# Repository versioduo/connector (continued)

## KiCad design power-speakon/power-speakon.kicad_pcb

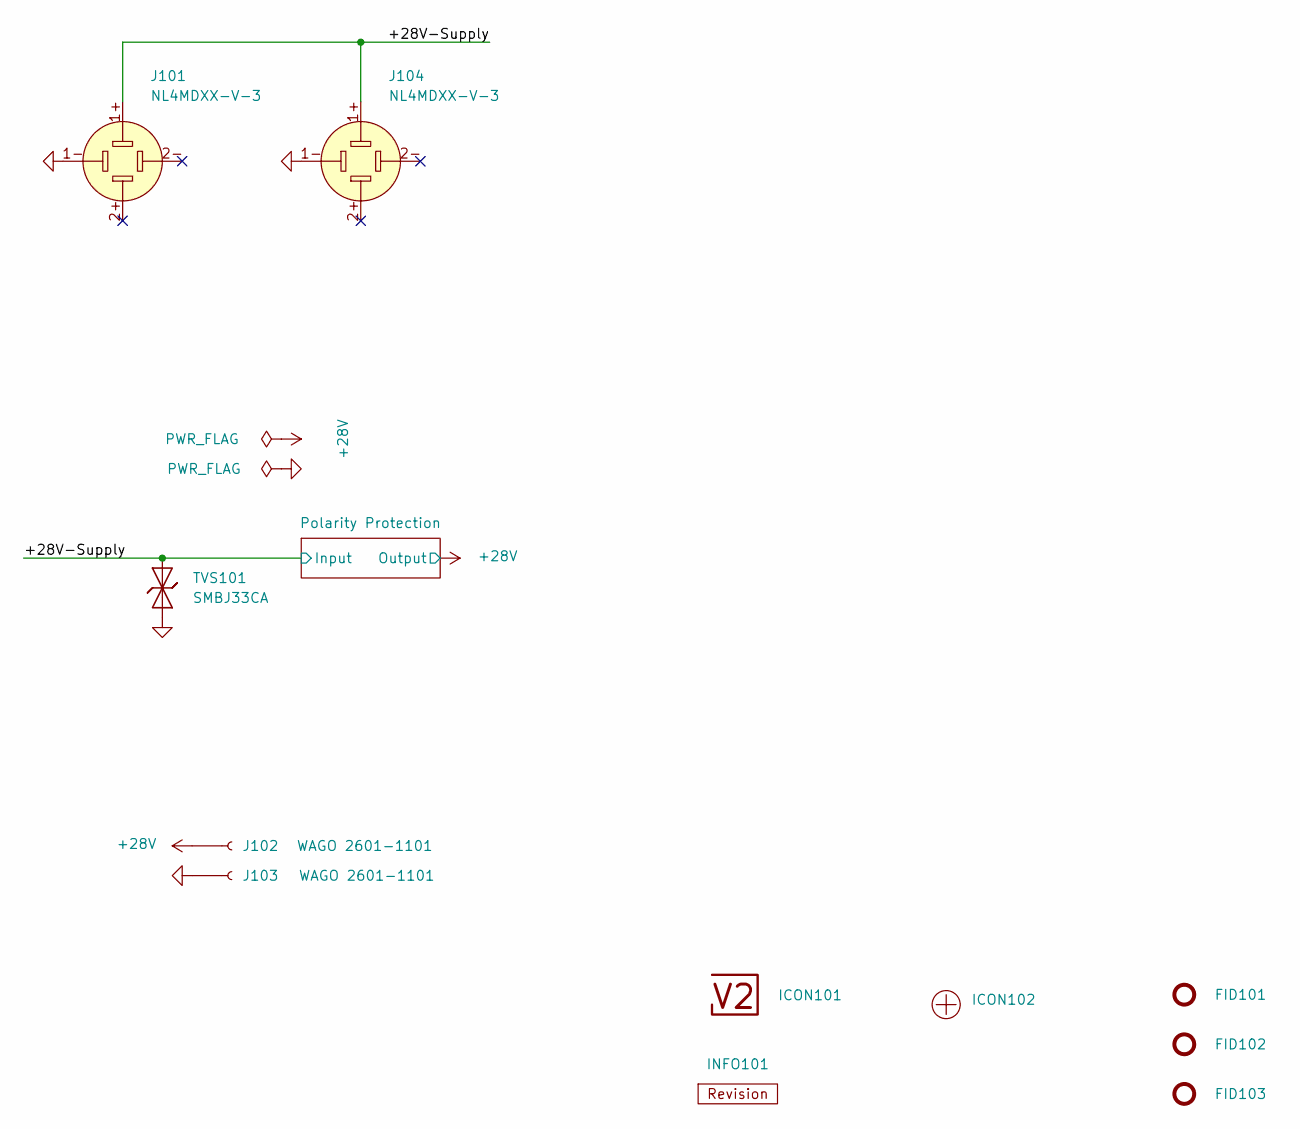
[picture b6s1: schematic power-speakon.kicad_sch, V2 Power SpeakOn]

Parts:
FID101, FID102, FID103: Fiducial_Paste; Fiducial_0.5mm_Mask1mm_Paste
ICON101: V2-logo; Logo_Small
ICON102: Plus; Plus_Small
INFO101: Revision
J101, J104: NL4MDXX-V-3; Mouser 568-NL4MDXXV3
J102, J103: WAGO 2601-1101; 2601-1101; Rating 17.5A
TVS101: SMBJ33CA; D_SMB; Rating 33V; Mouser 652-SMBJ33CA-Q

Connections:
+28V: J102.1; also elsewhere on the board
/+28V-Supply: J101.1+, J104.1+, TVS101.2 (A); also elsewhere on the board
GND: J101.1-, J103.1, J104.1-, TVS101.1 (K); also elsewhere on the board

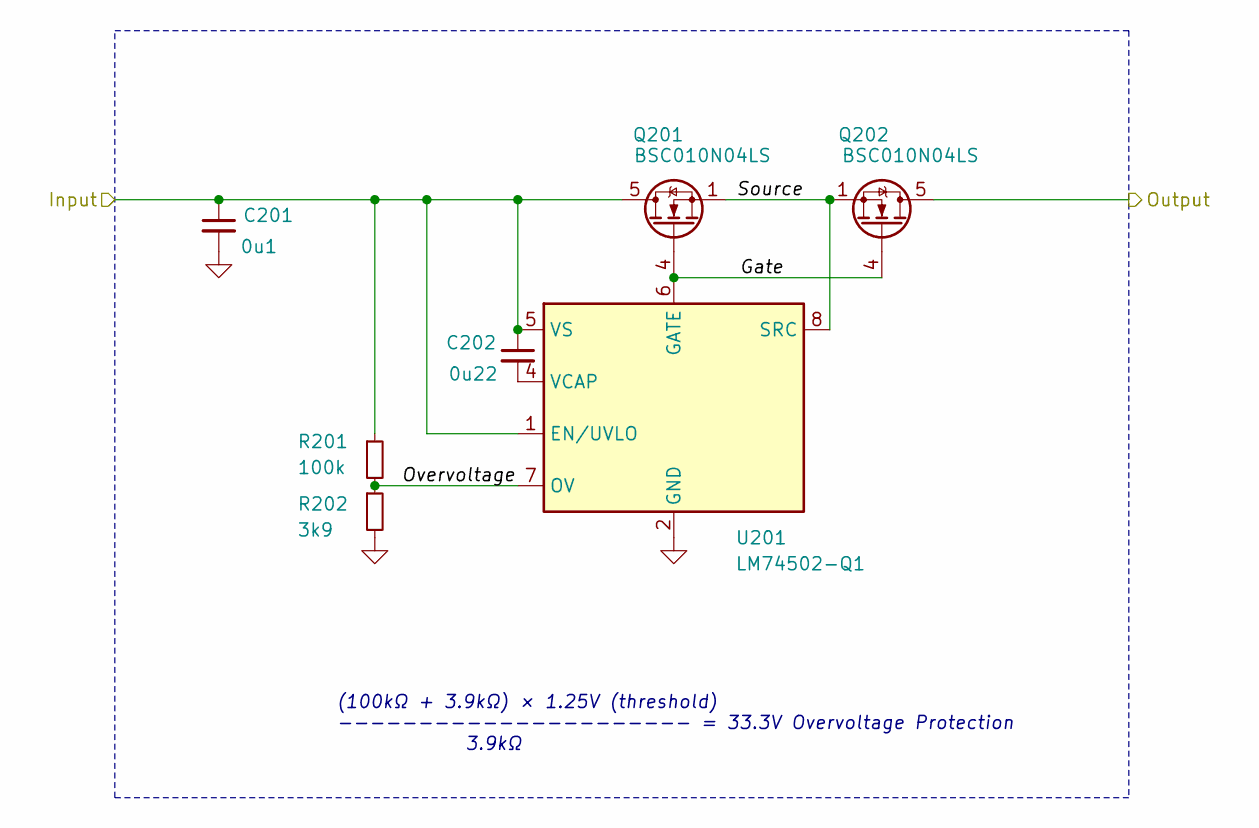
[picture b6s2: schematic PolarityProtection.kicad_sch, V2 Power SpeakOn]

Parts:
C201: 0u1; C_1608; Rating 50V; Mouser 810-CGA3E2X7R1H104MA
C202: 0u22; C_1608; Rating 50V; Mouser 603-CC0603JRX79BB224
Q201, Q202: BSC010N04LS; TDSON-8-FL; Rating 40V; Mouser 726-BSC010N04LS
R201: 100k; R_1608; Rating 100mW; Mouser 71-CRCW0603100KFKEAC
R202: 3k9; R_1608; Rating 100mW; Mouser 71-CRCW06033K90FKEAC
U201: LM74502-Q1; SOT-23-8; Rating 60uA; Mouser 595-LM74502QDDFRQ1

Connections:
+28V: Q202.5 (D); also elsewhere on the board
/+28V-Supply: C201.1, C202.1, Q201.5 (D), R201.1, U201.1 (EN/UVLO), U201.5 (VS); also elsewhere on the board
/Polarity Protection/Gate: Q201.4 (G), Q202.4 (G), U201.6 (GATE)
/Polarity Protection/Overvoltage: R201.2, R202.1, U201.7 (OV)
/Polarity Protection/Source: Q201.1 (S), Q202.1 (S), U201.8 (SRC)
GND: C201.2, R202.2, U201.2 (GND); also elsewhere on the board
unnamed: C202.2, U201.4 (VCAP)

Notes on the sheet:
(100kΩ + 3.9kΩ) × 1.25V (threshold) ---------------------- = 33.3V Overvoltage Protection 3.9kΩ

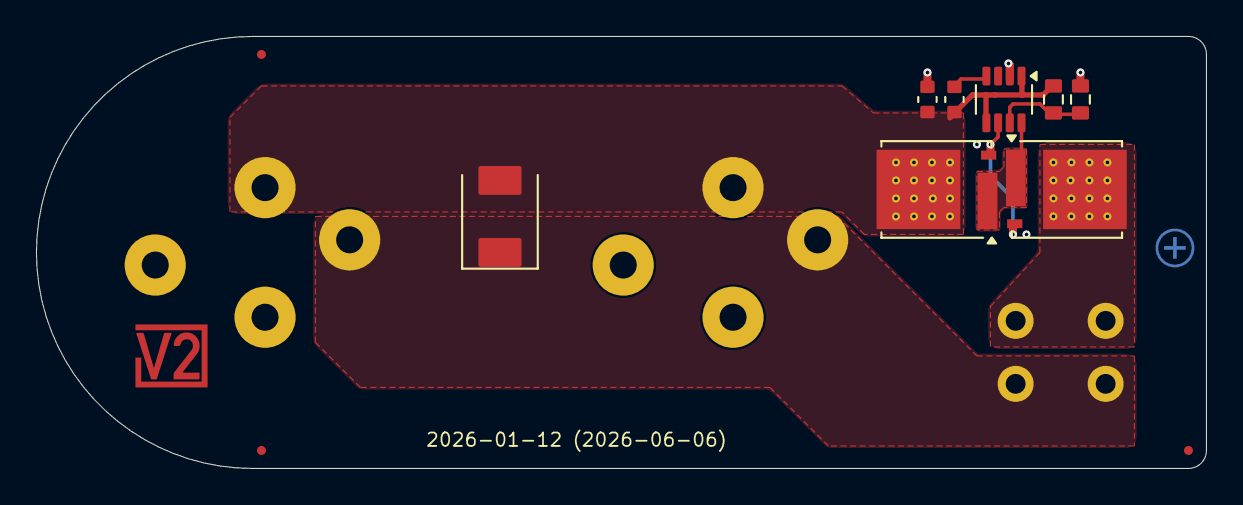
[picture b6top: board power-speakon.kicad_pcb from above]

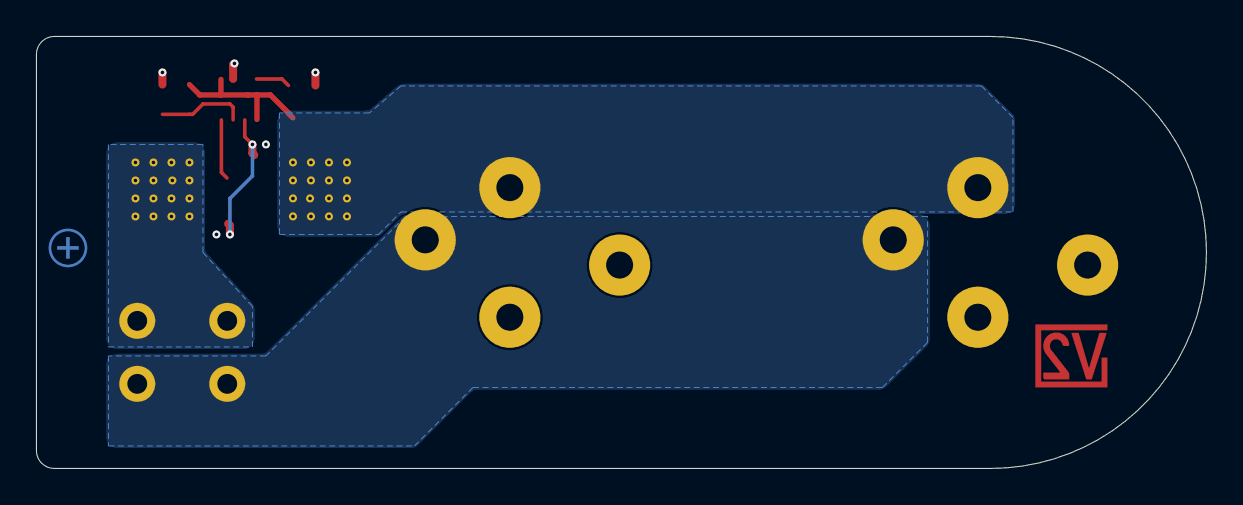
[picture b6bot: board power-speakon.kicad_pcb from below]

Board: 4 copper layers, 65.0 x 24.0 mm, 18 parts (5 on the bottom side), 7 nets.

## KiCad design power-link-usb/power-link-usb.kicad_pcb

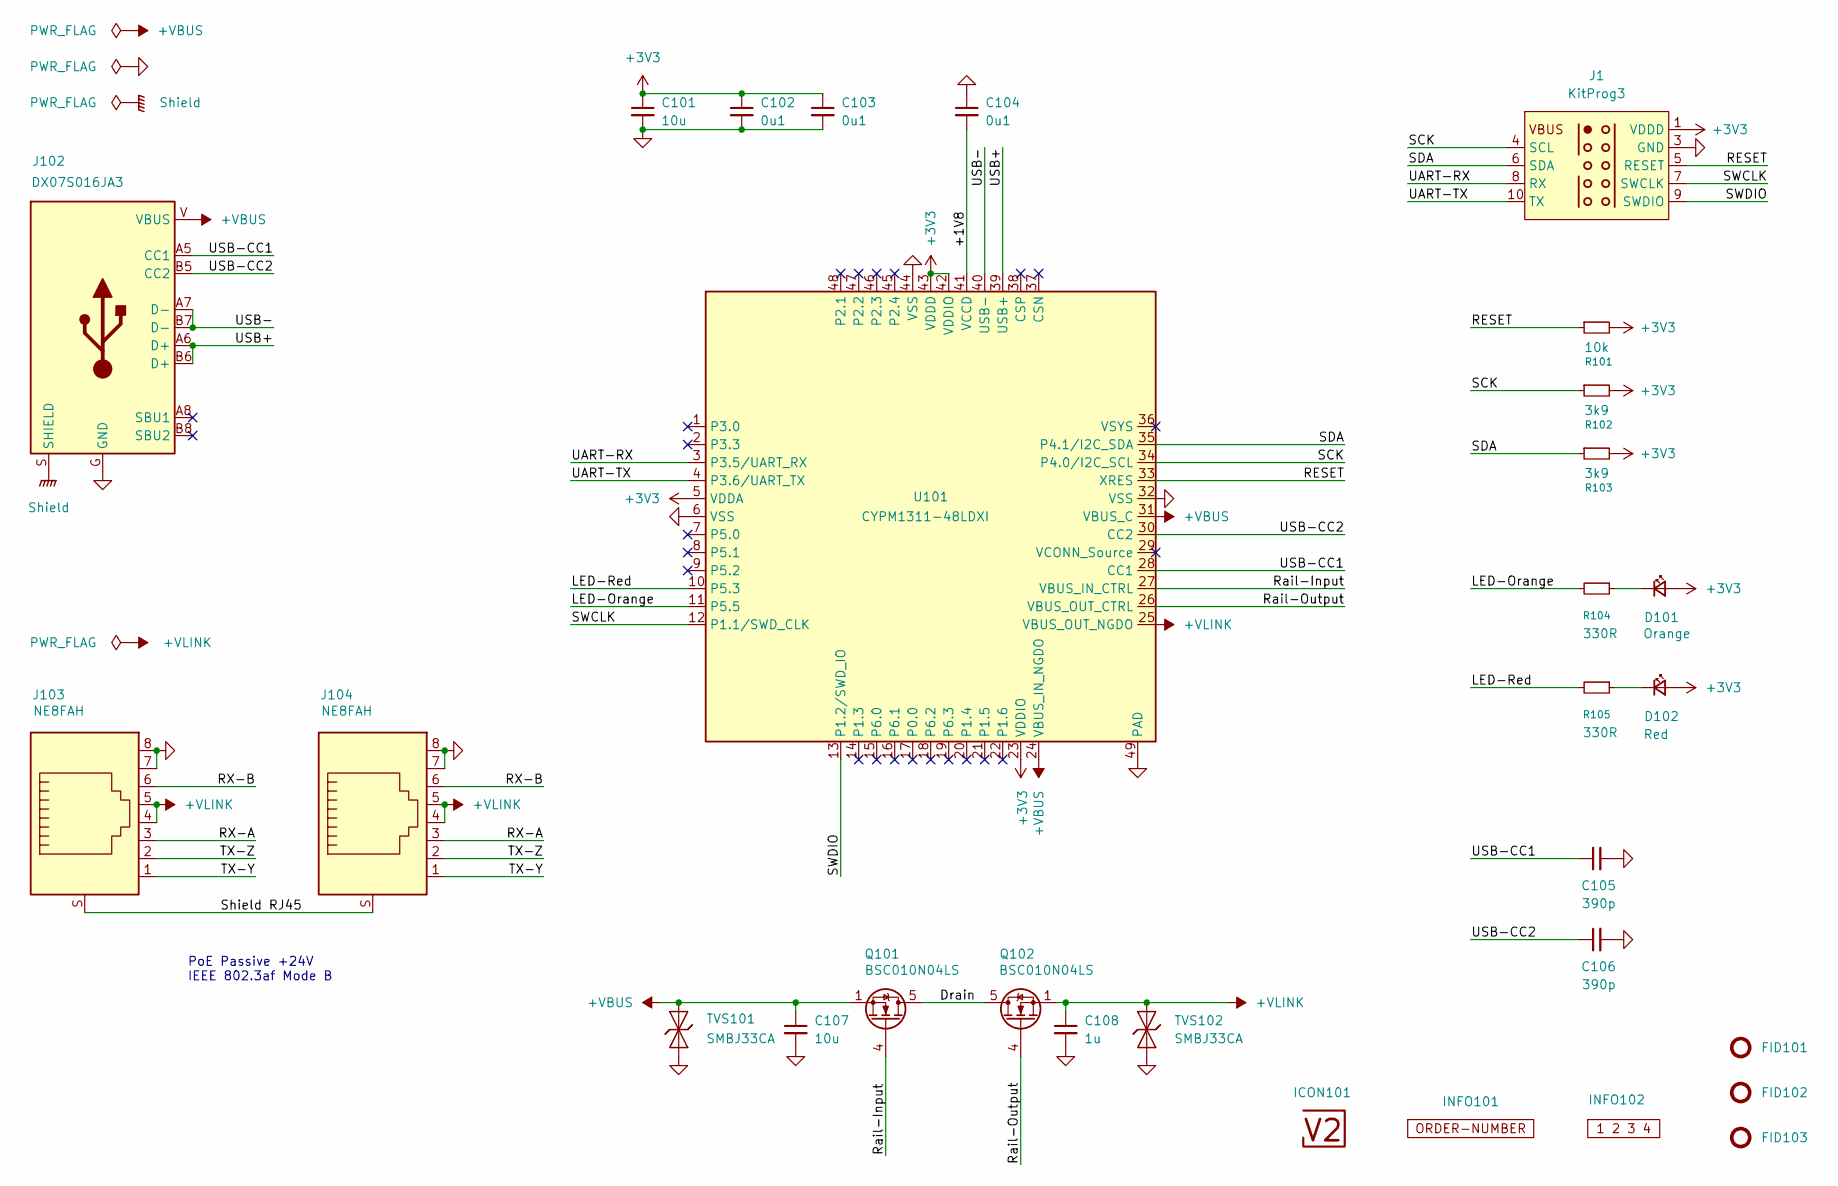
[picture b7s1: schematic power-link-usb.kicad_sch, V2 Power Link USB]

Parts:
C101: 10u; C_0603; Rating 10V; Mouser 810-C1608X6S1A106M
C102, C103, C104: 0u1; C_0603; Rating 50V; Mouser 810-CGA3E2X7R1H104MA
C105, C106: 390p; C_0603; Rating 50V; Mouser 810-CGA3E2C0G1H391J
C107: 10u; C_0805; Rating 25V; Mouser 810-C2012X5R1E106K
C108: 1u; C_0603; Rating 50V; Mouser 810-CGA3E3X7R1H105K0
D101: Orange; LED_0603; Mouser 755-SML-D12D1WT86
D102: Red; LED_0603; Mouser 755-SML-D12V1WT86
FID101, FID102, FID103: Fiducial_Paste; Fiducial_0.5mm_Mask1mm_Paste
ICON101: V2-logo; Logo_Small
INFO101: Order_Number
INFO102: Layer_Numbers
J1: KitProg3
J102: DX07S016JA3; JAE_DX07S016JA3; Mouser 656-DX07S016JA3R1500
J103, J104: NE8FAH; Mouser 568-NE8FAH
Q101, Q102: BSC010N04LS; TDSON-8-FL; Rating 40V; Mouser 726-BSC010N04LS
R101: 10k; R_0603; Rating 100mW; Mouser 71-CRCW060310K0FKEAC
R102, R103: 3k9; R_0603; Rating 100mW; Mouser 71-CRCW06033K90FKEAC
R104, R105: 330R; R_0603; Rating 100mW; Mouser 71-CRCW0603330RFKEAC
TVS101, TVS102: SMBJ33CA; D_SMB; Rating 33V; Mouser 652-SMBJ33CA-Q
U101: CYPM1311-48LDXI; QFN-48-1EP_6x6mm_P0.4mm_EP4.6x4.6mm; Mouser 727-CYPM1311-48LDXI

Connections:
+3V3: C101.1, C102.1, C103.1, D101.2 (A), D102.2 (A), J1.1 (VDDD), R101.2, R102.2, R103.2, U101.5 (VDDA), U101.23 (VDDIO), U101.42 (VDDIO), U101.43 (VDDD)
+VBUS: C107.1, J102.V (VBUS), Q101.1 (S), TVS101.2 (A), U101.24 (VBUS_IN_NGDO), U101.31 (VBUS_C)
+VLINK: C108.1, J103.4, J103.5, J104.4, J104.5, Q102.1 (S), TVS102.2 (A), U101.25 (VBUS_OUT_NGDO)
/+1V8: C104.2, U101.41 (VCCD)
/Drain: Q101.5 (D), Q102.5 (D)
/LED-Orange: R104.2, U101.11 (P5.5)
/LED-Red: R105.2, U101.10 (P5.3)
/RESET: J1.5 (RESET), R101.1, U101.33 (XRES)
/RX-A: J103.3, J104.3
/RX-B: J103.6, J104.6
/Rail-Input: Q101.4 (G), U101.27 (VBUS_IN_CTRL)
/Rail-Output: Q102.4 (G), U101.26 (VBUS_OUT_CTRL)
/SCK: J1.4 (SCL), R102.1, U101.34 (P4.0/I2C_SCL)
/SDA: J1.6 (SDA), R103.1, U101.35 (P4.1/I2C_SDA)
/SWCLK: J1.7 (SWCLK), U101.12 (P1.1/SWD_CLK)
/SWDIO: J1.9 (SWDIO), U101.13 (P1.2/SWD_IO)
/Shield RJ45: J103.S, J104.S
/TX-Y: J103.1, J104.1
/TX-Z: J103.2, J104.2
/UART-RX: J1.8 (RX), U101.3 (P3.5/UART_RX)
/UART-TX: J1.10 (TX), U101.4 (P3.6/UART_TX)
/USB+: J102.A6 (D+), J102.B6 (D+), U101.39 (USB+)
/USB-: J102.A7 (D-), J102.B7 (D-), U101.40 (USB-)
/USB-CC1: C105.1, J102.A5 (CC1), U101.28 (CC1)
/USB-CC2: C106.1, J102.B5 (CC2), U101.30 (CC2)
GND: C101.2, C102.2, C103.2, C104.1, C105.2, C106.2, C107.2, C108.2, J1.3 (GND), J102.G (GND), J103.7, J103.8, J104.7, J104.8, TVS101.1 (K), TVS102.1 (K), U101.6 (VSS), U101.32 (VSS), U101.44 (VSS), U101.49 (PAD)
unnamed: D101.1 (K), R104.1
unnamed: D102.1 (K), R105.1
Shield: J102.S (SHIELD)

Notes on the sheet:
PoE Passive +24V IEEE 802.3af Mode B

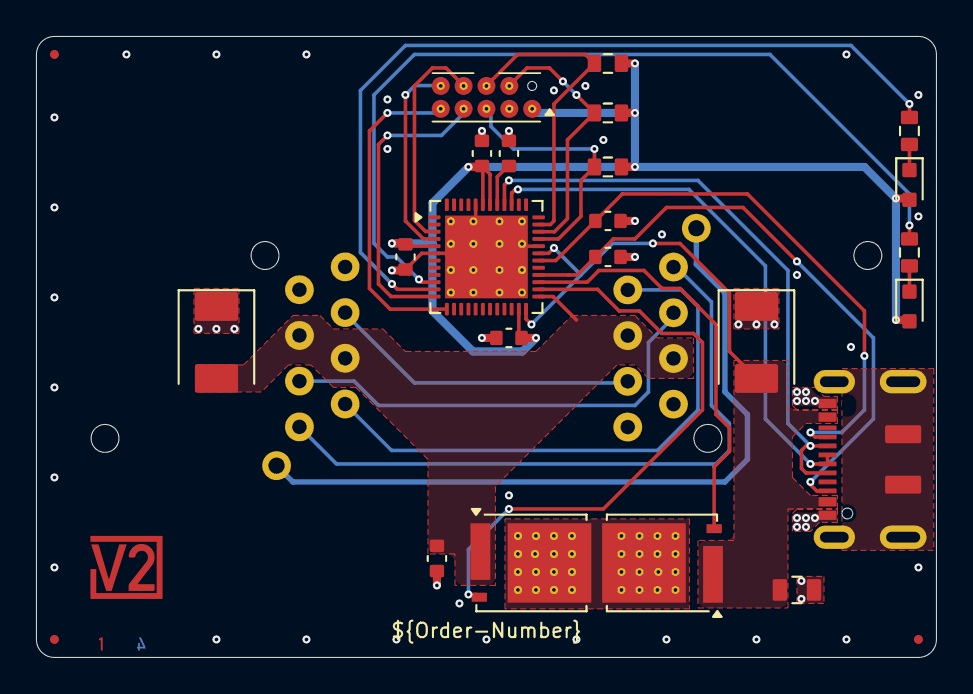
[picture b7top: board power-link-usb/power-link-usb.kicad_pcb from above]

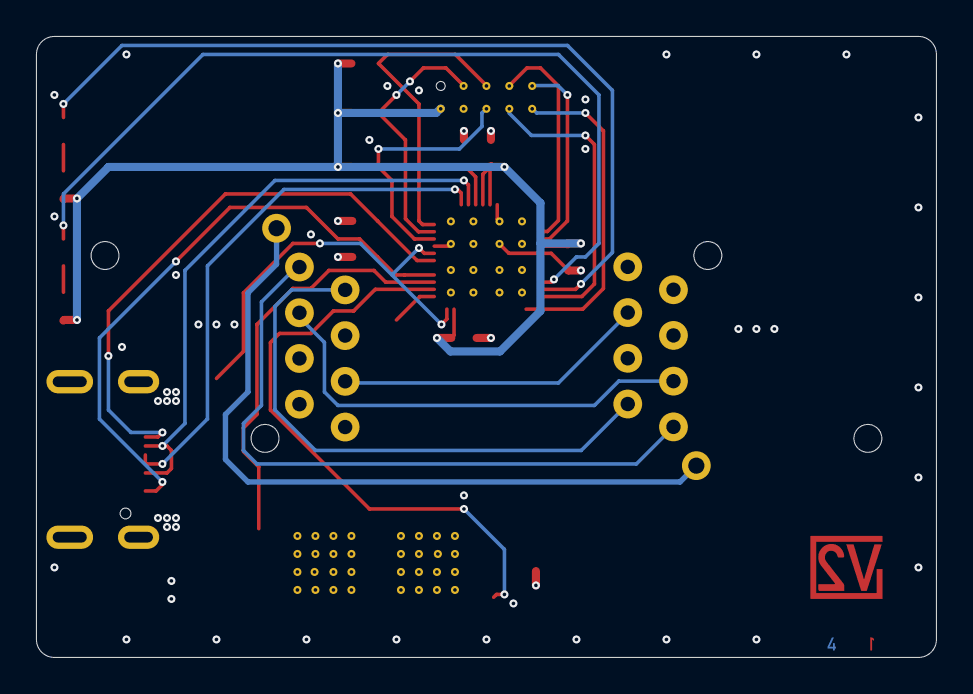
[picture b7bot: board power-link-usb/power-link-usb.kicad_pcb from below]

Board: 4 copper layers, 50.0 x 34.5 mm, 30 parts (2 on the bottom side), 28 nets.

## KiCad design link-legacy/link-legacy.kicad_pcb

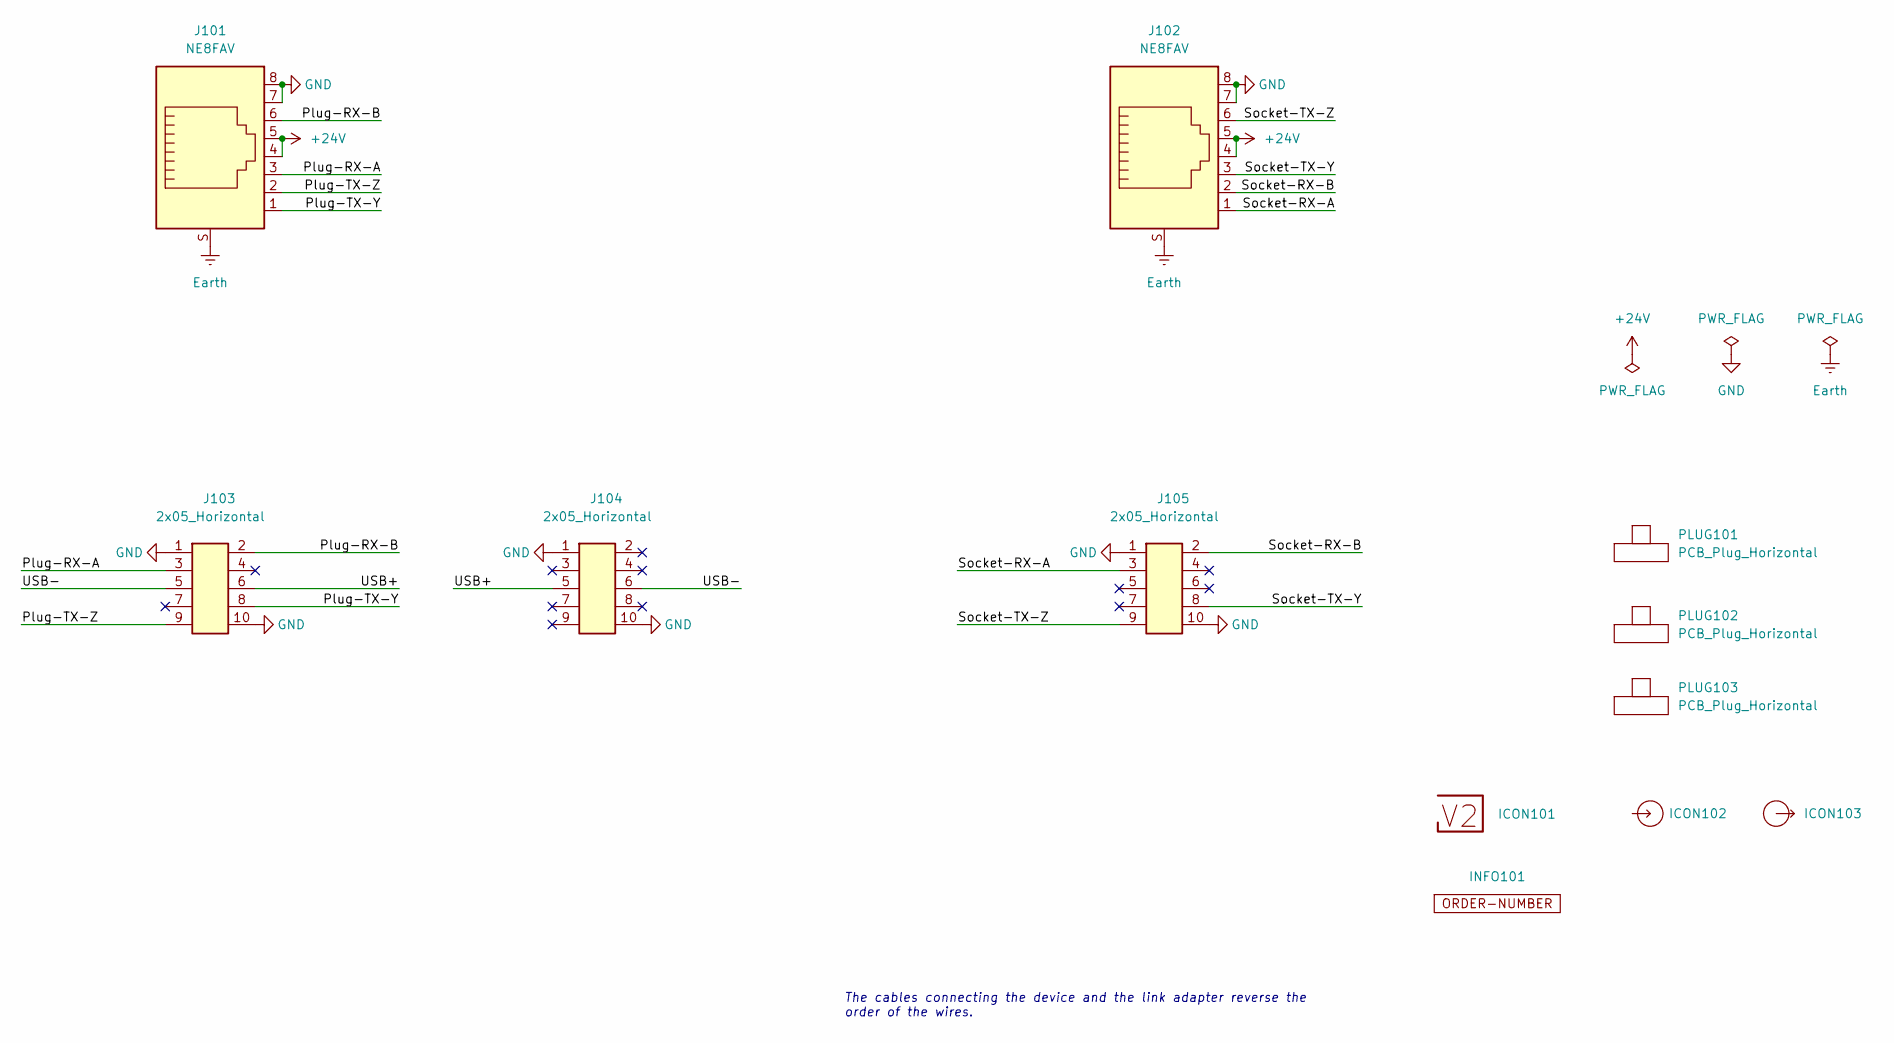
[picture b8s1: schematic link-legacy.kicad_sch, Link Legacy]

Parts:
ICON101: V2-logo; Logo_Small
ICON102: Arrow_In
ICON103: Arrow_Out
INFO101: ORDER-NUMBER; Order_Number
J101, J102: NE8FAV
J103, J104, J105: 2x05_Horizontal; PinHeader_2x05_P1.27mm_Horizontal
PLUG101, PLUG102, PLUG103: PCB_Plug_Horizontal

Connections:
+24V: J101.4, J101.5, J102.4, J102.5
/Plug-RX-A: J101.3, J103.3
/Plug-RX-B: J101.6, J103.2
/Plug-TX-Y: J101.1, J103.8
/Plug-TX-Z: J101.2, J103.9
/Socket-RX-A: J102.1, J105.3
/Socket-RX-B: J102.2, J105.2
/Socket-TX-Y: J102.3, J105.8
/Socket-TX-Z: J102.6, J105.9
/USB+: J103.6, J104.5
/USB-: J103.5, J104.6
Earth: J101.S, J102.S
GND: J101.7, J101.8, J102.7, J102.8, J103.1, J103.10, J104.1, J104.10, J105.1, J105.10

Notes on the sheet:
The cables connecting the device and the link adapter reverse the order of the wires.

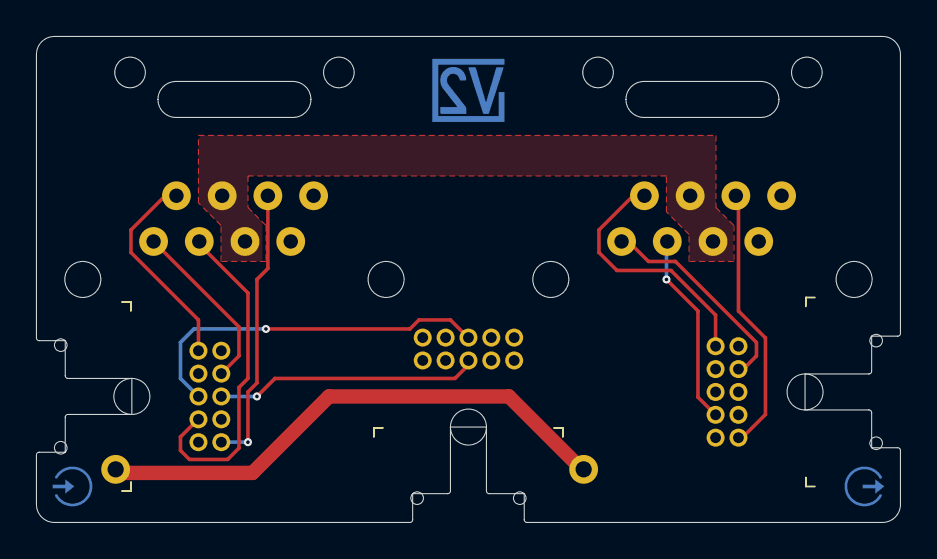
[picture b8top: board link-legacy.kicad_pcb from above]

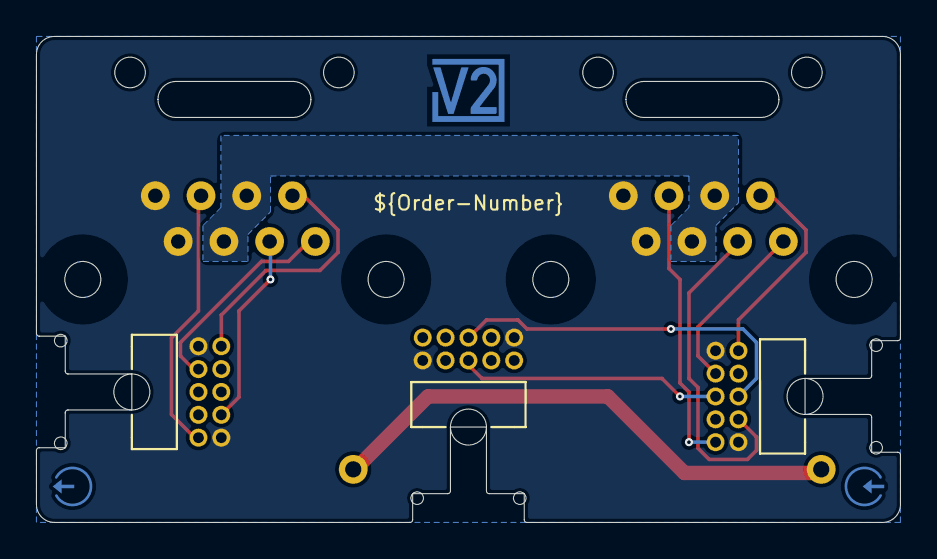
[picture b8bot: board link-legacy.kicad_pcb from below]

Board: 2 copper layers, 48.0 x 27.0 mm, 12 parts (7 on the bottom side), 13 nets.

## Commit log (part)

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2025-11-17 Import
2025-11-28 Link termination
2025-11-28 Colours
2025-12-07 Refresh
2026-01-01 Add power-speakon
2026-01-10 Add usb
2026-01-11 Update usb + link-poe
2026-01-12 Update power symbols
2026-01-14 Update parts
2026-01-19 Rename power-poe -> power-link-wago
2026-01-21 Add power-link-usb
2026-01-23 Fix WAGOs
2026-01-26 Update power-link-usb
2026-02-01 Update library
2026-02-03 Add comment
2026-02-09 Add usb firmware
2026-02-10 Use date as revision
2026-02-13 Replace Order_Number
2026-02-14 power-link-usb: refuse 5V contract
2026-02-25 Export stencil
2026-03-31 Replace step-down
2026-04-08 power-link-usb: split out PowerDelivery
2026-04-24 Update DRC
2026-05-11 Good Bye Imperial
